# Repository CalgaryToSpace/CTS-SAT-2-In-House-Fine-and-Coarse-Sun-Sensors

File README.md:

# CTS-SAT-2-In-House-ADCS
Repository for CTS SAT-2 in-house ADCS components. Fine and coarse sun sensors

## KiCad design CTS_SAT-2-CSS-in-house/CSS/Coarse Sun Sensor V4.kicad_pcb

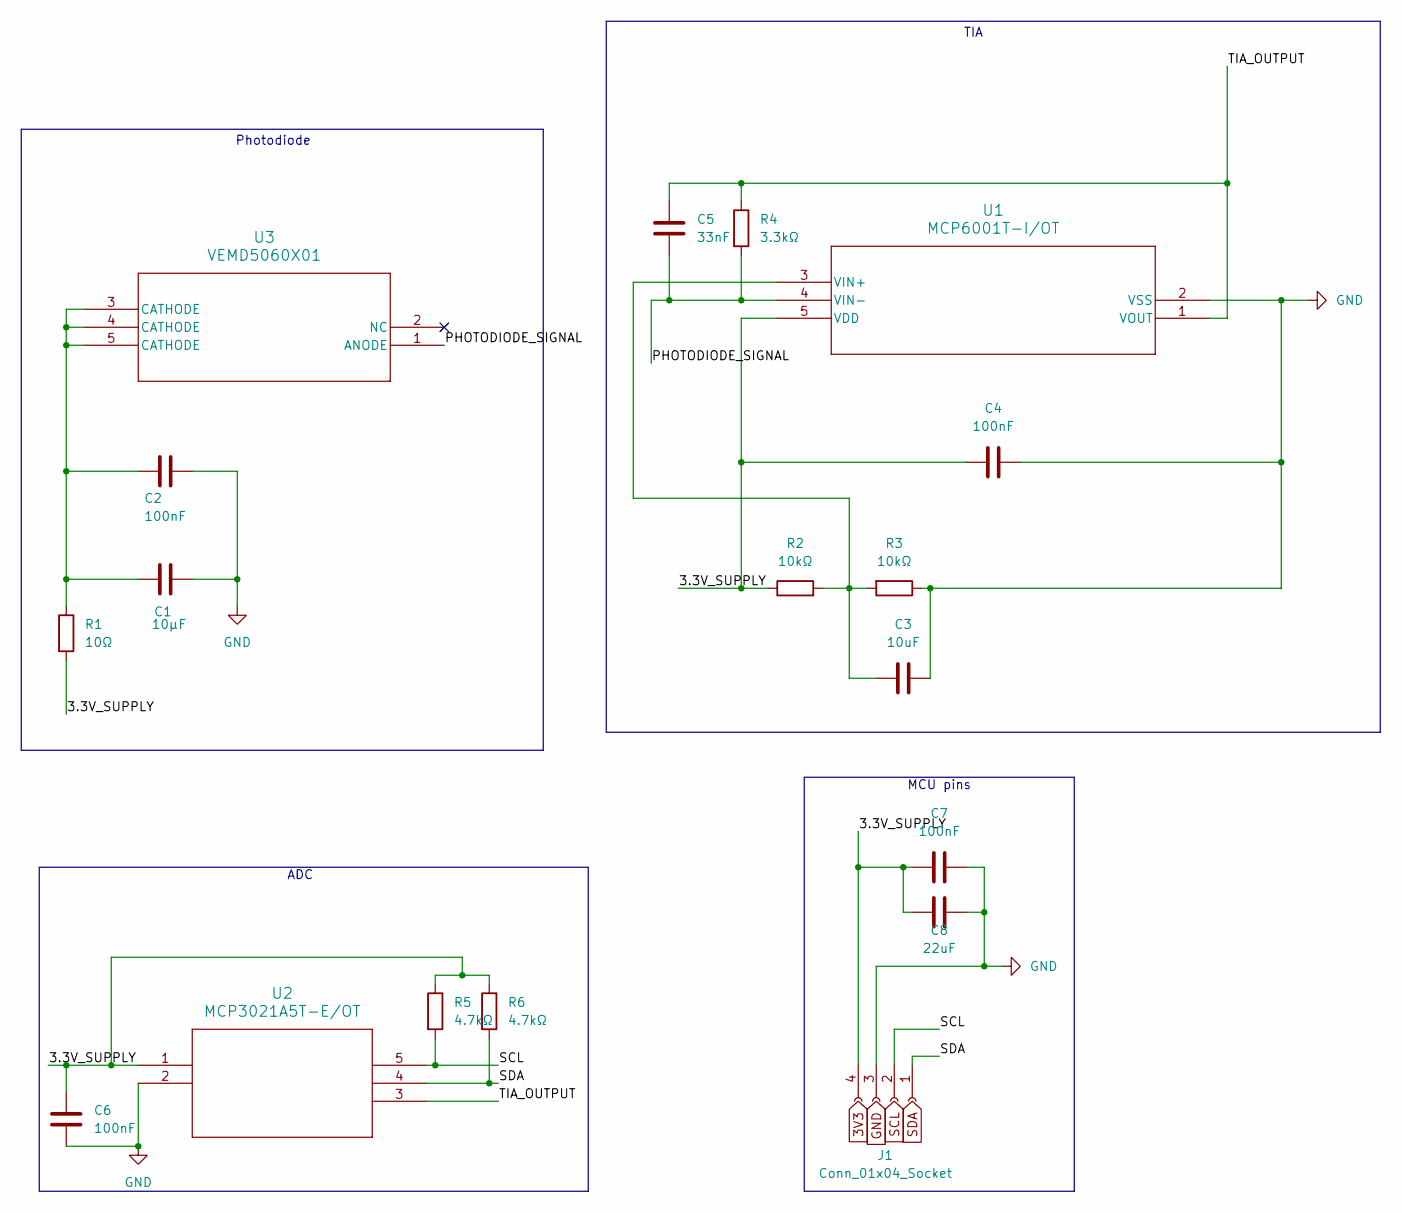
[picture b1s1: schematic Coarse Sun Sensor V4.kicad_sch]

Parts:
C1: 10μF; C_0805_2012Metric_Pad1.18x1.45mm_HandSolder
C2, C4, C6, C7: 100nF; C_0805_2012Metric_Pad1.18x1.45mm_HandSolder
C3: 10uF; C_0805_2012Metric_Pad1.18x1.45mm_HandSolder
C5: 33nF; C_0805_2012Metric_Pad1.18x1.45mm_HandSolder
C8: 22uF; C_0805_2012Metric_Pad1.18x1.45mm_HandSolder
J1: Conn_01x04_Socket; PinHeader_1x04_P2.54mm_Vertical_SMD_Pin1Left
R1: 10Ω; R_0805_2012Metric_Pad1.20x1.40mm_HandSolder
R2, R3: 10kΩ; R_0805_2012Metric_Pad1.20x1.40mm_HandSolder
R4: 3.3kΩ; R_0805_2012Metric_Pad1.20x1.40mm_HandSolder
R5, R6: 4.7kΩ; R_0805_2012Metric_Pad1.20x1.40mm_HandSolder
U1: MCP6001T-I/OT; SOT-23-5_MC_MCH
U2: MCP3021A5T-E/OT; SOT-23-5_MC_MCH
U3: VEMD5060X01; SMD_VEMD5-5X4_VIS

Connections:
/3.3V_SUPPLY: C4.1, C6.2, C7.1, C8.2, J1.4, R1.2, R2.1, R5.1, R6.1, U1.5 (VDD), U2.1
/PHOTODIODE_SIGNAL: C5.2, R4.2, U1.4 (VIN-), U3.1 (ANODE)
/TIA_OUTPUT: C5.1, R4.1, U1.1 (VOUT), U2.3
GND: C1.2, C2.2, C3.2, C4.2, C6.1, C7.2, C8.1, J1.3, R3.1, U1.2 (VSS), U2.2
unnamed: C1.1, C2.1, R1.1, U3.3 (CATHODE), U3.4 (CATHODE), U3.5 (CATHODE)
unnamed: C3.1, R2.2, R3.2, U1.3 (VIN+)
SCL: J1.2, R5.2, U2.5
SDA: J1.1, R6.2, U2.4

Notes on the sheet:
Photodiode
MCU pins
TIA
ADC

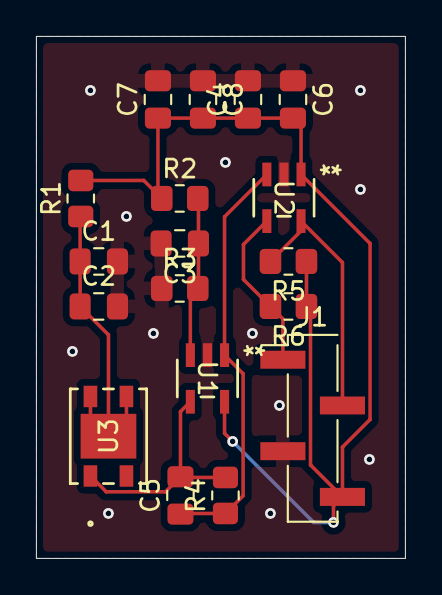
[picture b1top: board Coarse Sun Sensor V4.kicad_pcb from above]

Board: 2 copper layers, 20.5 x 29.0 mm, 18 parts (0 on the bottom side), 8 nets.

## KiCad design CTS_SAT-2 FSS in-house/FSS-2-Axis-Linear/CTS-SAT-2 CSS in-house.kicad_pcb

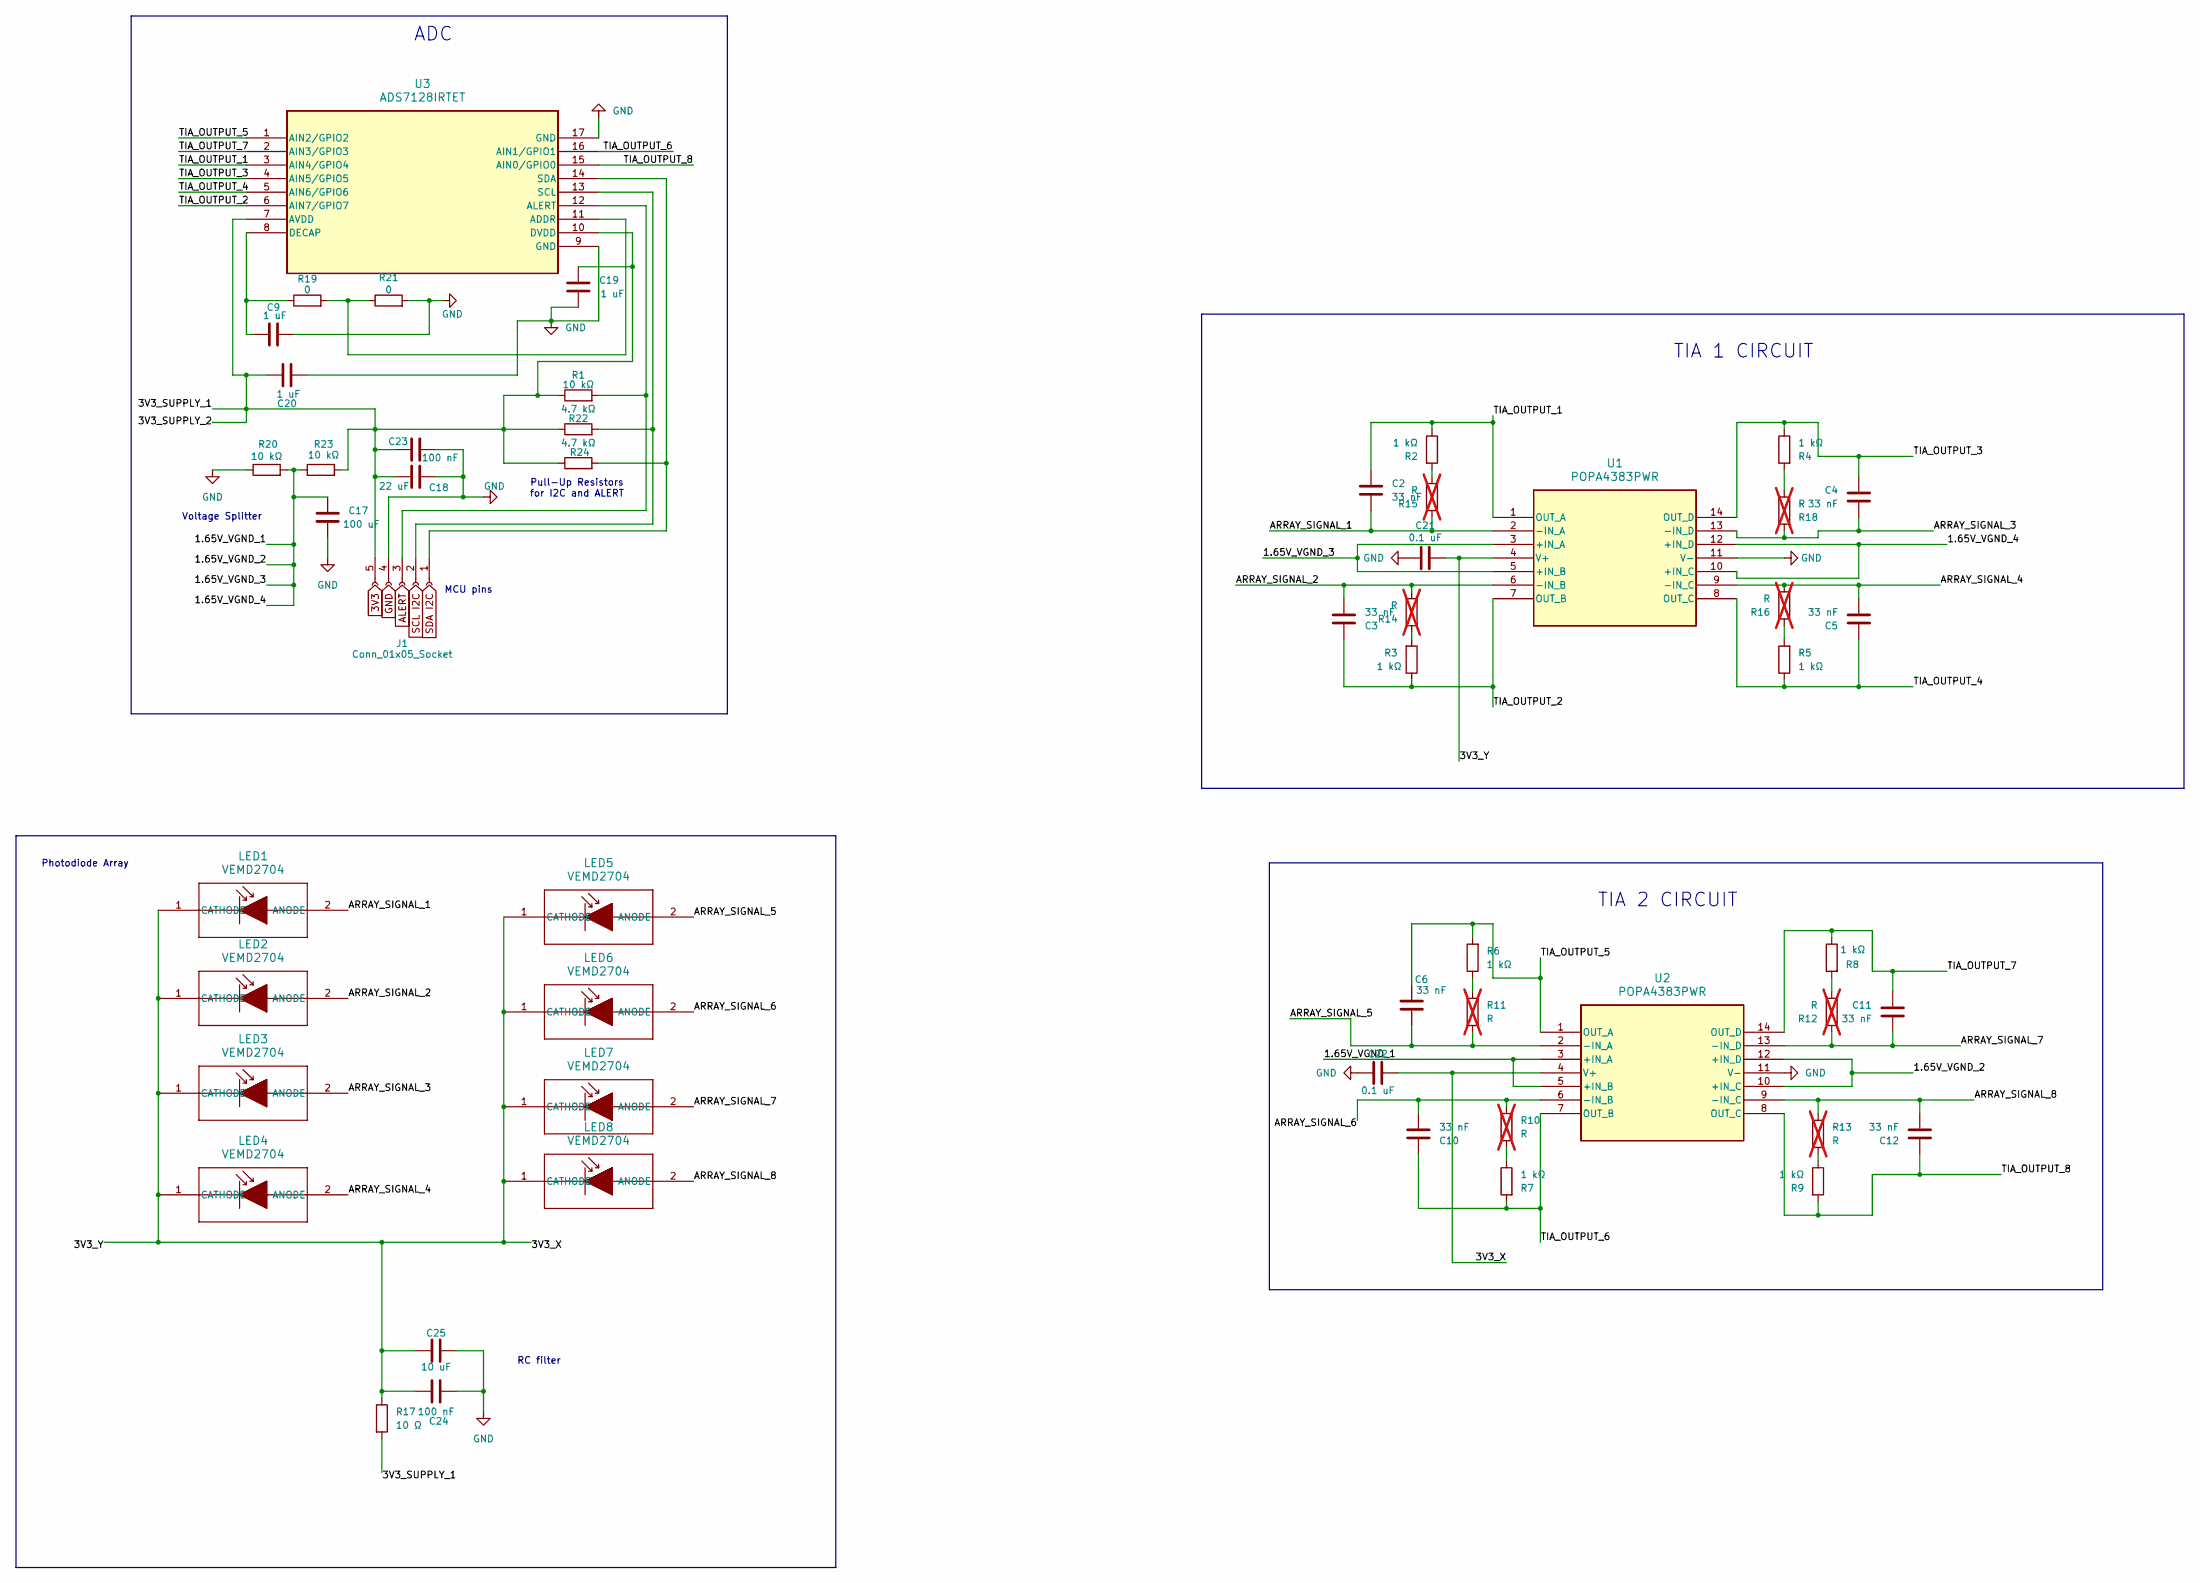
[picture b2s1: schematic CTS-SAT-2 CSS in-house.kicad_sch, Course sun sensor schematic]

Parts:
C2, C3, C4, C5, C6, C10, C11, C12: 33 nF; C_0603_1608Metric_Pad1.08x0.95mm_HandSolder
C9, C19, C20: 1 uF; C_0603_1608Metric_Pad1.08x0.95mm_HandSolder
C17: 100 uF; C_0603_1608Metric_Pad1.08x0.95mm_HandSolder
C18: 22 uF; C_0603_1608Metric_Pad1.08x0.95mm_HandSolder
C21, C22: 0.1 uF; C_0603_1608Metric_Pad1.08x0.95mm_HandSolder
C23, C24: 100 nF; C_0603_1608Metric_Pad1.08x0.95mm_HandSolder
C25: 10 uF; C_0603_1608Metric_Pad1.08x0.95mm_HandSolder
J1: Conn_01x05_Socket; PinHeader_1x05_P2.54mm_Vertical_SMD_Pin1Left
LED1, LED2, LED3, LED4, LED5, LED6, LED7, LED8: VEMD2704; VEMD2704_VIS
R1, R20, R23: 10 kΩ; R_0603_1608Metric_Pad0.98x0.95mm_HandSolder
R2, R3, R4, R5, R6, R7, R8, R9: 1 kΩ; R_0603_1608Metric_Pad0.98x0.95mm_HandSolder
R10, R11, R12, R13, R14, R15, R16, R18: R; R_0603_1608Metric_Pad0.98x0.95mm_HandSolder; not fitted
R17: 10 Ω; R_0603_1608Metric_Pad0.98x0.95mm_HandSolder
R19, R21: 0; R_0603_1608Metric_Pad0.98x0.95mm_HandSolder
R22, R24: 4.7 kΩ; R_0603_1608Metric_Pad0.98x0.95mm_HandSolder
U1, U2: POPA4383PWR; TSSOP_PW_14_TEX
U3: ADS7128IRTET; WQFN16_RTE_TEX

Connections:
/1.65V_VGND_1: C17.1, R20.2, R23.1, U1.3 (+IN_A), U1.5 (+IN_B), U1.10 (+IN_C), U1.12 (+IN_D), U2.3 (+IN_A), U2.5 (+IN_B), U2.10 (+IN_C), U2.12 (+IN_D)
/3V3_SUPPLY_1: C18.1, C19.1, C20.1, C23.1, J1.5, R1.1, R17.2, R22.1, R23.2, R24.1, U3.7 (AVDD), U3.10 (DVDD)
/3V3_X: C21.1, C22.1, C24.1, C25.2, LED1.1 (CATHODE), LED2.1 (CATHODE), LED3.1 (CATHODE), LED4.1 (CATHODE), LED5.1 (CATHODE), LED6.1 (CATHODE), LED7.1 (CATHODE), LED8.1 (CATHODE), R17.1, U1.4 (V+), U2.4 (V+)
/ARRAY_SIGNAL_1: C2.1, LED1.2 (ANODE), R15.1, U1.2 (-IN_A)
/ARRAY_SIGNAL_2: C3.1, LED2.2 (ANODE), R14.2, U1.6 (-IN_B)
/ARRAY_SIGNAL_3: C4.1, LED3.2 (ANODE), R18.2, U1.13 (-IN_D)
/ARRAY_SIGNAL_4: C5.1, LED4.2 (ANODE), R16.2, U1.9 (-IN_C)
/ARRAY_SIGNAL_5: C6.1, LED5.2 (ANODE), R11.2, U2.2 (-IN_A)
/ARRAY_SIGNAL_6: C10.1, LED6.2 (ANODE), R10.1, U2.6 (-IN_B)
/ARRAY_SIGNAL_7: C11.1, LED7.2 (ANODE), R12.1, U2.13 (-IN_D)
/ARRAY_SIGNAL_8: C12.1, LED8.2 (ANODE), R13.1, U2.9 (-IN_C)
/TIA_OUTPUT_1: C2.2, R2.1, U1.1 (OUT_A), U3.3 (AIN4/GPIO4)
/TIA_OUTPUT_2: C3.2, R3.1, U1.7 (OUT_B), U3.6 (AIN7/GPIO7)
/TIA_OUTPUT_3: C4.2, R4.1, U1.14 (OUT_D), U3.4 (AIN5/GPIO5)
/TIA_OUTPUT_4: C5.2, R5.1, U1.8 (OUT_C), U3.5 (AIN6/GPIO6)
/TIA_OUTPUT_5: C6.2, R6.2, U2.1 (OUT_A), U3.1 (AIN2/GPIO2)
/TIA_OUTPUT_6: C10.2, R7.2, U2.7 (OUT_B), U3.16 (AIN1/GPIO1)
/TIA_OUTPUT_7: C11.2, R8.1, U2.14 (OUT_D), U3.2 (AIN3/GPIO3)
/TIA_OUTPUT_8: C12.2, R9.2, U2.8 (OUT_C), U3.15 (AIN0/GPIO0)
GND: C9.1, C17.2, C18.2, C19.2, C20.2, C21.2, C22.2, C23.2, C24.2, C25.1, J1.4, R20.1, R21.2, U1.11 (V-), U2.11 (V-), U3.9 (GND), U3.17 (GND)
unnamed: J1.1, R24.2, U3.14 (SDA)
unnamed: J1.2, R22.2, U3.13 (SCL)
unnamed: J1.3, R1.2, U3.12 (ALERT)
unnamed: R7.1, R10.2
unnamed: R6.1, R11.1
unnamed: R8.2, R12.2
unnamed: R9.1, R13.2
unnamed: R3.2, R14.1
unnamed: R2.2, R15.2
unnamed: R5.2, R16.1
unnamed: R4.2, R18.1
unnamed: R19.2, R21.1, U3.11 (ADDR)
unnamed: C9.2, R19.1, U3.8 (DECAP)

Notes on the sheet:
TIA 1 CIRCUIT
RC filter
MCU pins
Voltage Splitter
Photodiode Array
Pull-Up Resistors for I2C and ALERT
ADC
TIA 2 CIRCUIT

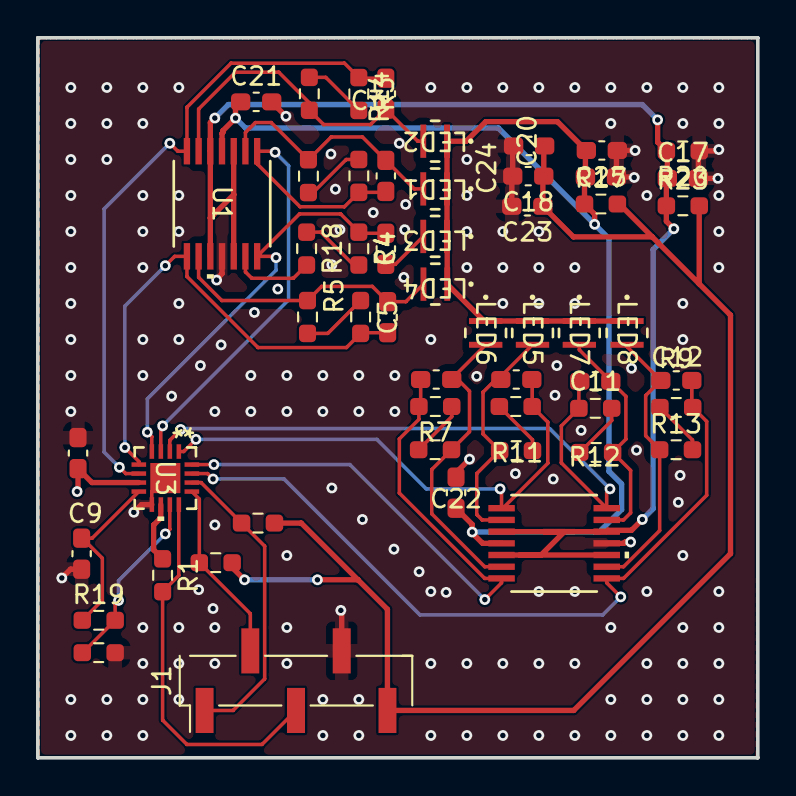
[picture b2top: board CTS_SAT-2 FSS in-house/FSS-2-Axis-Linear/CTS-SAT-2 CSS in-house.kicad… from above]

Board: 2 copper layers, 40.0 x 40.0 mm, 54 parts (0 on the bottom side), 33 nets.

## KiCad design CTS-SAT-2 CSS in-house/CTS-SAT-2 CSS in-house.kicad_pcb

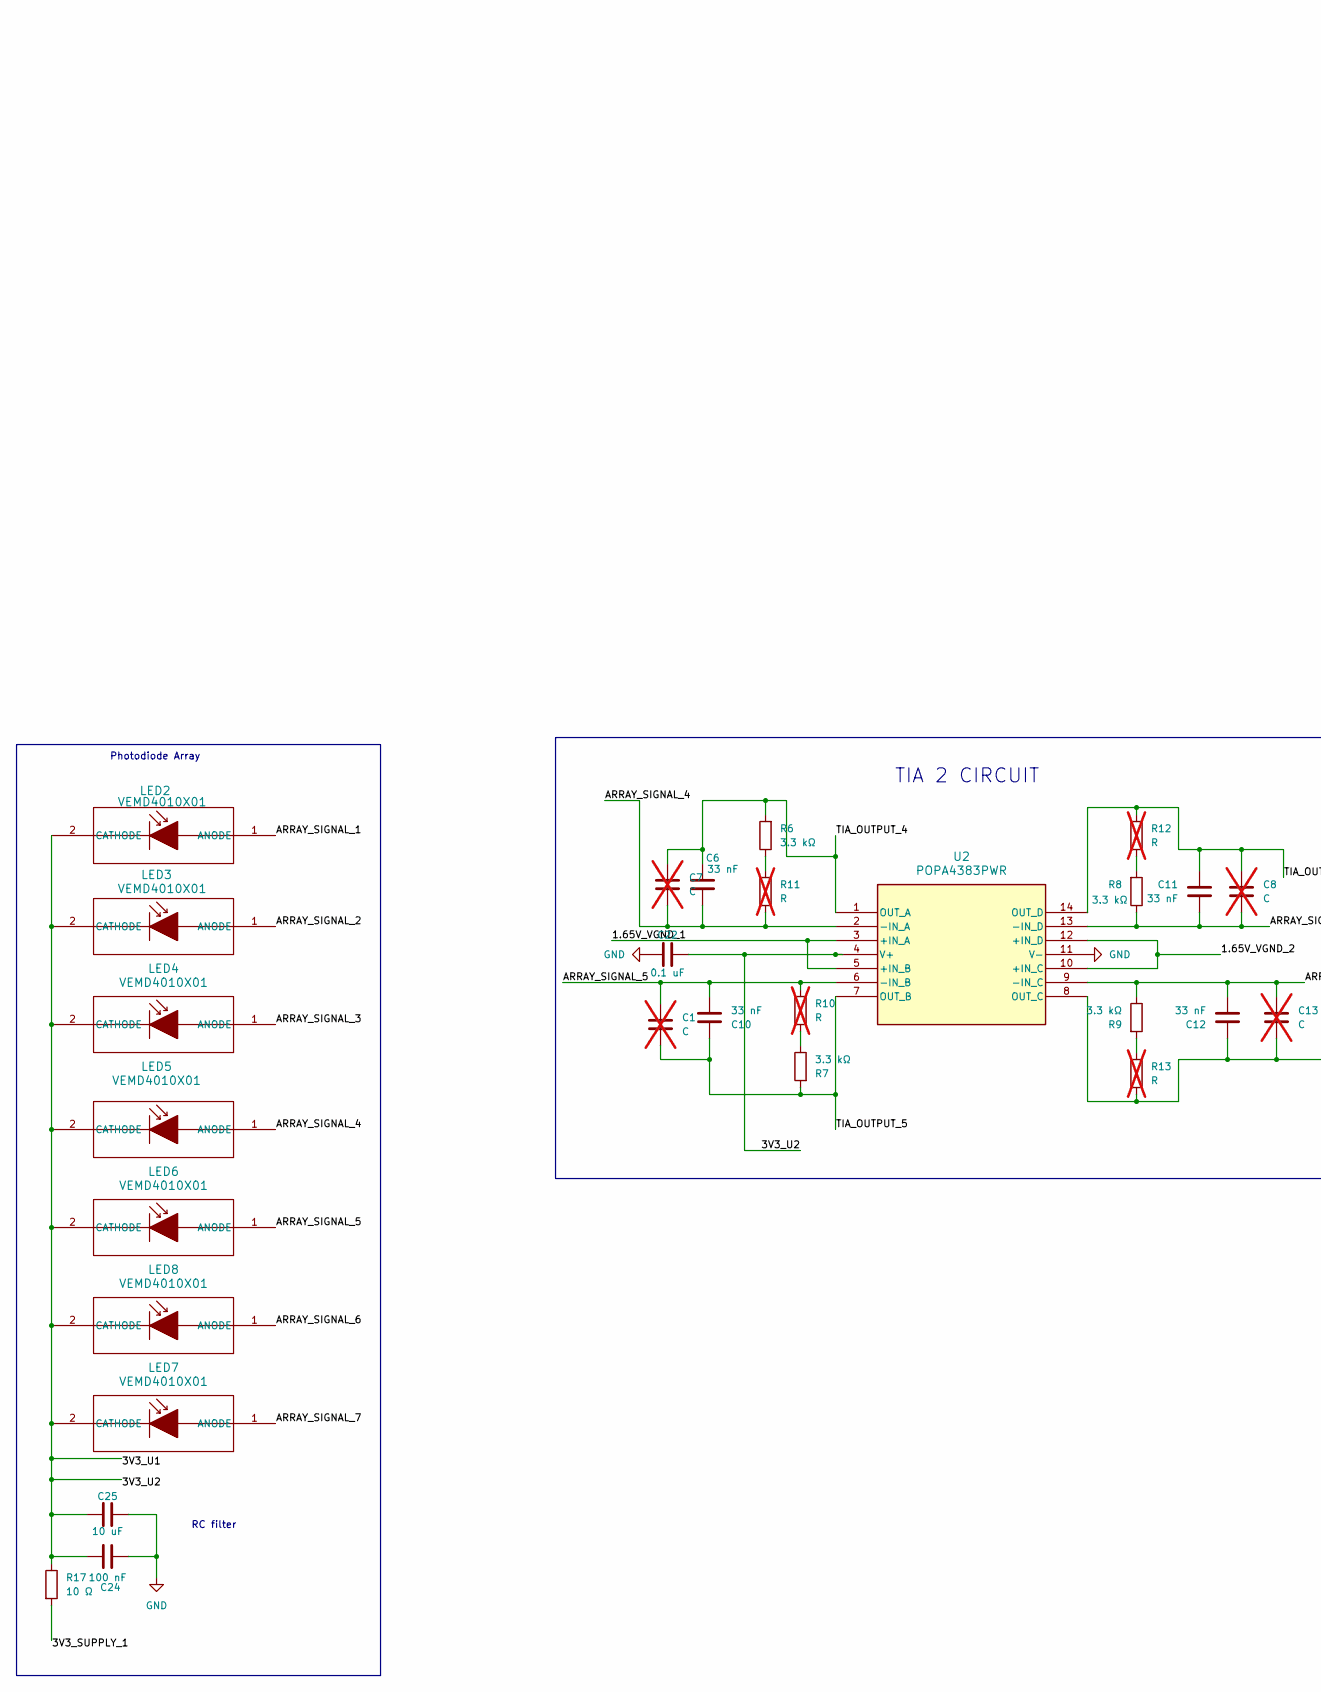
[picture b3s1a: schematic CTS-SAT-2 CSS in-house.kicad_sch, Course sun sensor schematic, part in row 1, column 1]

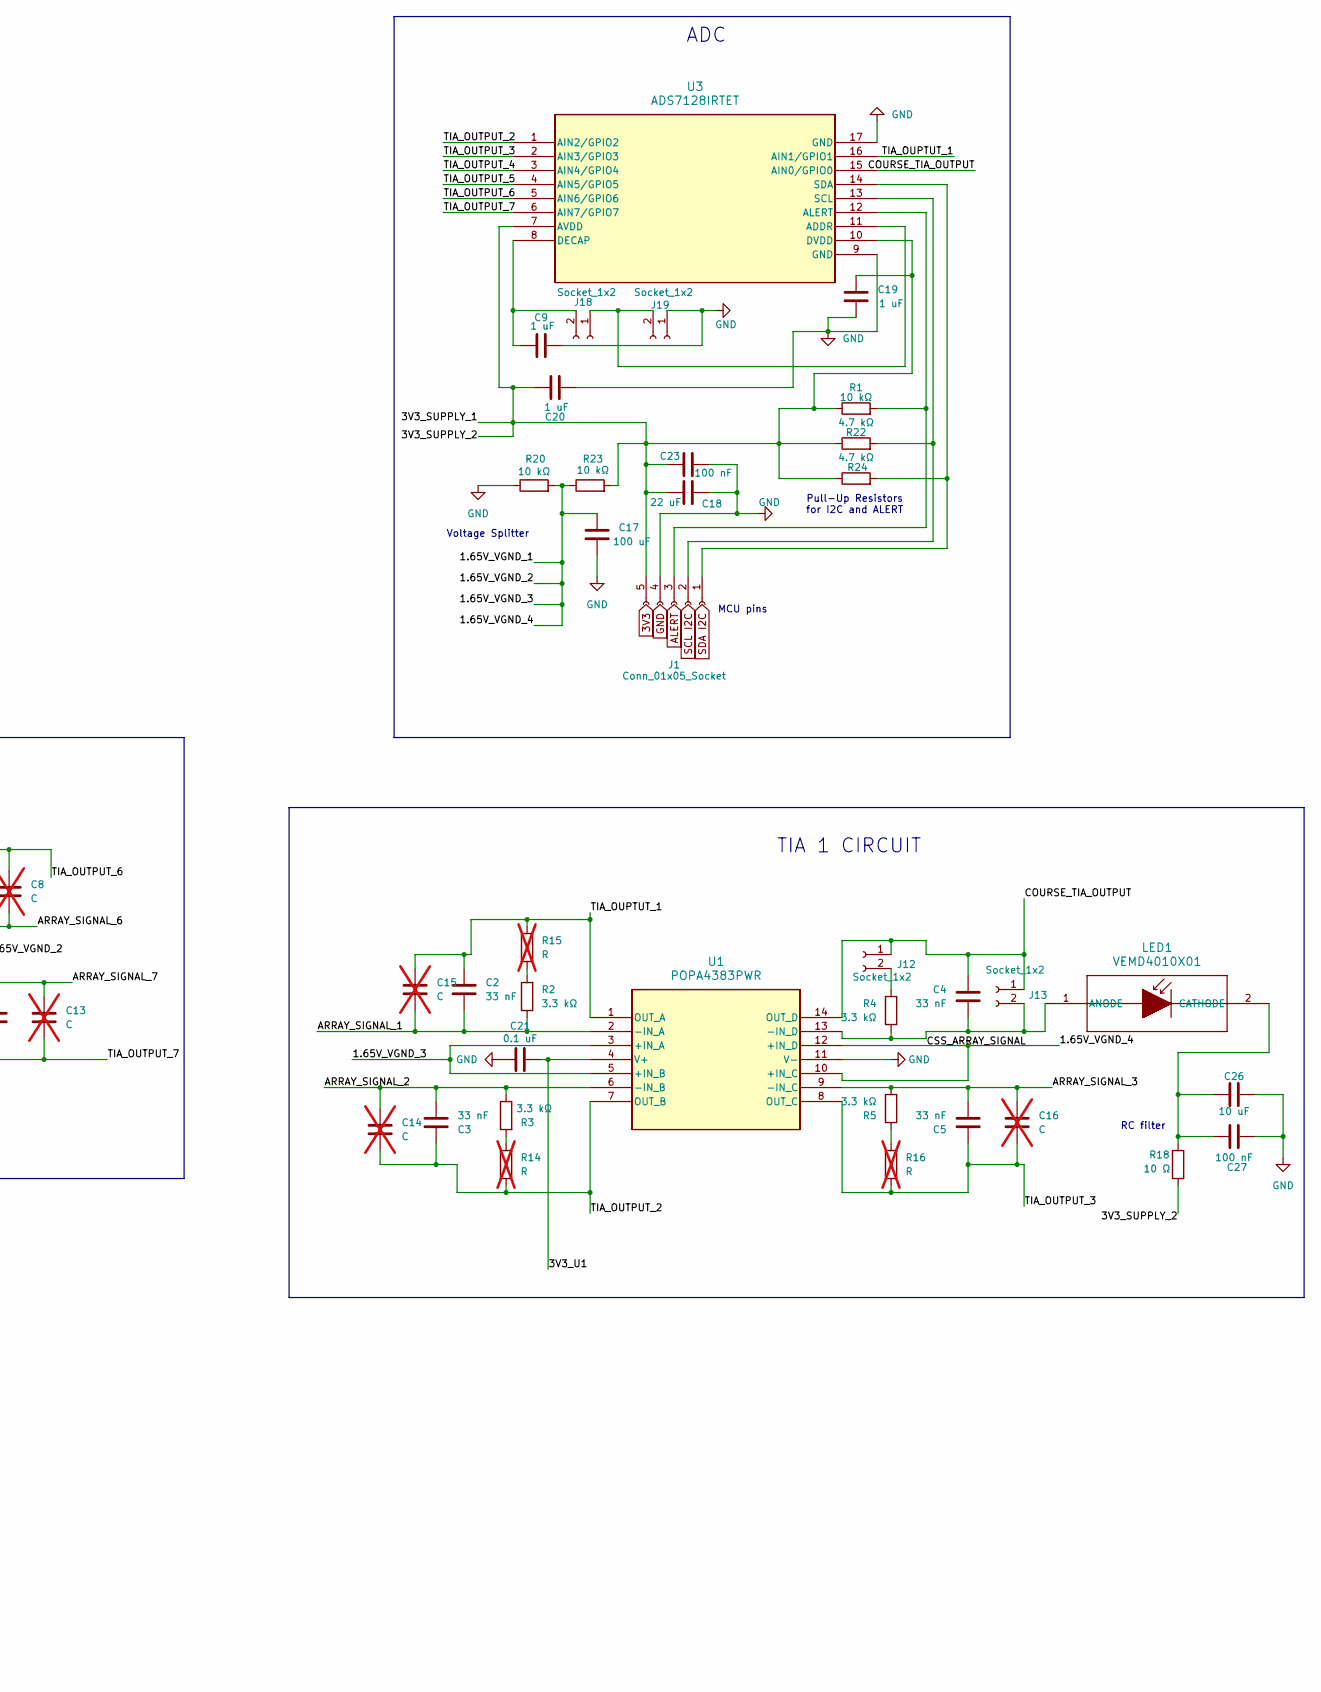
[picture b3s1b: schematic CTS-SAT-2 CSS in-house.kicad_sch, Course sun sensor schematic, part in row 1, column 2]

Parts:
C1, C7, C8, C13, C14, C15, C16: C; C_0603_1608Metric_Pad1.08x0.95mm_HandSolder; not fitted
C2, C3, C4, C5, C6, C10, C11, C12: 33 nF; C_0603_1608Metric_Pad1.08x0.95mm_HandSolder
C9, C19, C20: 1 uF; C_0603_1608Metric_Pad1.08x0.95mm_HandSolder
C17: 100 uF; C_0603_1608Metric_Pad1.08x0.95mm_HandSolder
C18: 22 uF; C_0603_1608Metric_Pad1.08x0.95mm_HandSolder
C21, C22: 0.1 uF; C_0603_1608Metric_Pad1.08x0.95mm_HandSolder
C23, C24, C27: 100 nF; C_0603_1608Metric_Pad1.08x0.95mm_HandSolder
C25, C26: 10 uF; C_0603_1608Metric_Pad1.08x0.95mm_HandSolder
J1: Conn_01x05_Socket; PinHeader_1x05_P2.54mm_Vertical_SMD_Pin1Left
J12, J13, J18, J19: Socket_1x2; PinSocket_1x02_P2.54mm_Vertical_SMD_Pin1Left
LED1, LED2, LED3, LED4, LED5, LED6, LED7, LED8: VEMD4010X01; 6p550-5363p01-4_VIS
R1, R20, R23: 10 kΩ; R_0603_1608Metric_Pad0.98x0.95mm_HandSolder
R2, R3, R4, R5, R6, R7, R8, R9: 3.3 kΩ; R_0603_1608Metric_Pad0.98x0.95mm_HandSolder
R10, R11, R12, R13, R14, R15, R16: R; R_0603_1608Metric_Pad0.98x0.95mm_HandSolder; not fitted
R17, R18: 10 Ω; C_0603_1608Metric_Pad1.08x0.95mm_HandSolder
R22, R24: 4.7 kΩ; R_0603_1608Metric_Pad0.98x0.95mm_HandSolder
U1, U2: POPA4383PWR; TSSOP_PW_14_TEX
U3: ADS7128IRTET; WQFN16_RTE_TEX

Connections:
/1.65V_VGND_1: C17.1, R20.2, R23.1, U1.3 (+IN_A), U1.5 (+IN_B), U1.10 (+IN_C), U1.12 (+IN_D), U2.3 (+IN_A), U2.5 (+IN_B), U2.10 (+IN_C), U2.12 (+IN_D)
/3V3_SUPPLY_1: C18.1, C19.1, C20.1, C23.1, J1.5, R1.1, R17.2, R18.2, R22.1, R23.2, R24.1, U3.7 (AVDD), U3.10 (DVDD)
/3V3_U1: C21.1, C22.1, C24.1, C25.2, LED2.2 (CATHODE), LED3.2 (CATHODE), LED4.2 (CATHODE), LED5.2 (CATHODE), LED6.2 (CATHODE), LED7.2 (CATHODE), LED8.2 (CATHODE), R17.1, U1.4 (V+), U2.4 (V+)
/ARRAY_SIGNAL_1: C2.1, C15.2, LED2.1 (ANODE), R2.1, U1.2 (-IN_A)
/ARRAY_SIGNAL_2: C3.1, C14.1, LED3.1 (ANODE), R3.1, U1.6 (-IN_B)
/ARRAY_SIGNAL_3: C5.1, C16.1, LED4.1 (ANODE), R5.1, U1.9 (-IN_C)
/ARRAY_SIGNAL_4: C6.1, C7.2, LED5.1 (ANODE), R11.2, U2.2 (-IN_A)
/ARRAY_SIGNAL_5: C1.1, C10.1, LED6.1 (ANODE), R10.1, U2.6 (-IN_B)
/ARRAY_SIGNAL_6: C8.2, C11.1, LED8.1 (ANODE), R8.1, U2.13 (-IN_D)
/ARRAY_SIGNAL_7: C12.1, C13.1, LED7.1 (ANODE), R9.1, U2.9 (-IN_C)
/COURSE_TIA_OUTPUT: C4.2, J12.1, J13.1, U1.14 (OUT_D), U3.15 (AIN0/GPIO0)
/CSS_ARRAY_SIGNAL: C4.1, J13.2, LED1.1 (ANODE), R4.1, U1.13 (-IN_D)
/TIA_OUPTUT_1: C2.2, C15.1, R15.1, U1.1 (OUT_A), U3.16 (AIN1/GPIO1)
/TIA_OUTPUT_2: C3.2, C14.2, R14.2, U1.7 (OUT_B), U3.1 (AIN2/GPIO2)
/TIA_OUTPUT_3: C5.2, C16.2, R16.2, U1.8 (OUT_C), U3.2 (AIN3/GPIO3)
/TIA_OUTPUT_4: C6.2, C7.1, R6.2, U2.1 (OUT_A), U3.3 (AIN4/GPIO4)
/TIA_OUTPUT_5: C1.2, C10.2, R7.2, U2.7 (OUT_B), U3.4 (AIN5/GPIO5)
/TIA_OUTPUT_6: C8.1, C11.2, R12.1, U2.14 (OUT_D), U3.5 (AIN6/GPIO6)
/TIA_OUTPUT_7: C12.2, C13.2, R13.2, U2.8 (OUT_C), U3.6 (AIN7/GPIO7)
GND: C9.1, C17.2, C18.2, C19.2, C20.2, C21.2, C22.2, C23.2, C24.2, C25.1, C26.1, C27.2, J1.4, J19.1, R20.1, U1.11 (V-), U2.11 (V-), U3.9 (GND), U3.17 (GND)
unnamed: J1.1, R24.2, U3.14 (SDA)
unnamed: J1.2, R22.2, U3.13 (SCL)
unnamed: J1.3, R1.2, U3.12 (ALERT)
unnamed: J12.2, R4.2
unnamed: J18.1, J19.2, U3.11 (ADDR)
unnamed: C9.2, J18.2, U3.8 (DECAP)
unnamed: C26.2, C27.1, LED1.2 (CATHODE), R18.1
unnamed: R7.1, R10.2
unnamed: R6.1, R11.1
unnamed: R8.2, R12.2
unnamed: R9.2, R13.1
unnamed: R3.2, R14.1
unnamed: R2.2, R15.2
unnamed: R5.2, R16.1

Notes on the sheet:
TIA 1 CIRCUIT
RC filter
MCU pins
Voltage Splitter
Photodiode Array
Pull-Up Resistors for I2C and ALERT
ADC
TIA 2 CIRCUIT

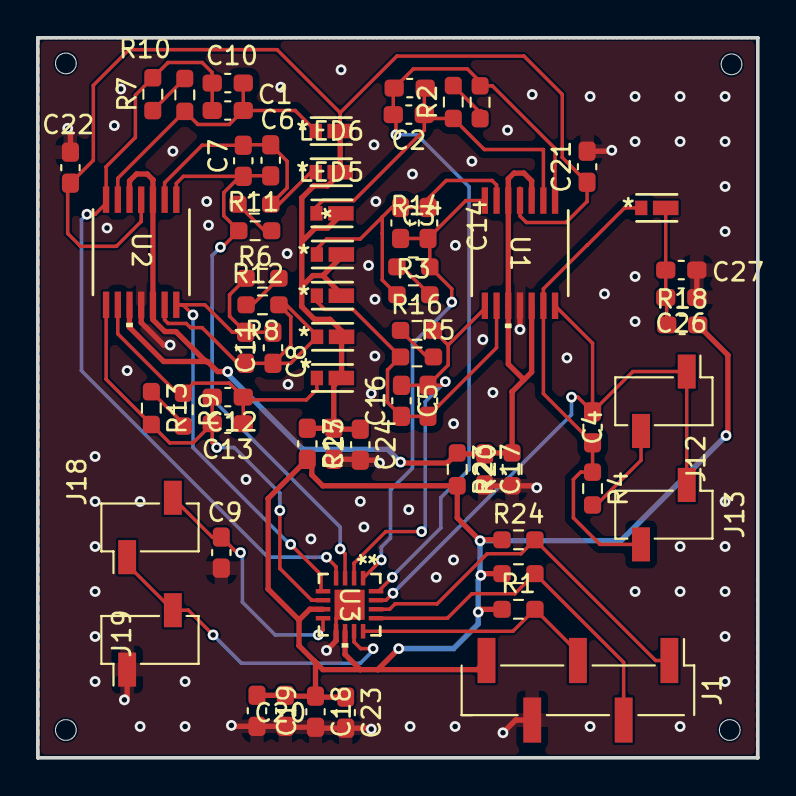
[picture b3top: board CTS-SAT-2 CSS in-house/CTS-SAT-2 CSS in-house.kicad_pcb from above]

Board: 2 copper layers, 40.0 x 40.0 mm, 65 parts (0 on the bottom side), 34 nets.
